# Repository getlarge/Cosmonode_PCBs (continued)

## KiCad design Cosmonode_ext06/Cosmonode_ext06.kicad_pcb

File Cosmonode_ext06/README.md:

# Cosmonode_ext_06

Extension 6  : - BNC connector for ph probe 
	       - 5V signal converted to 3.3V

Work in progress

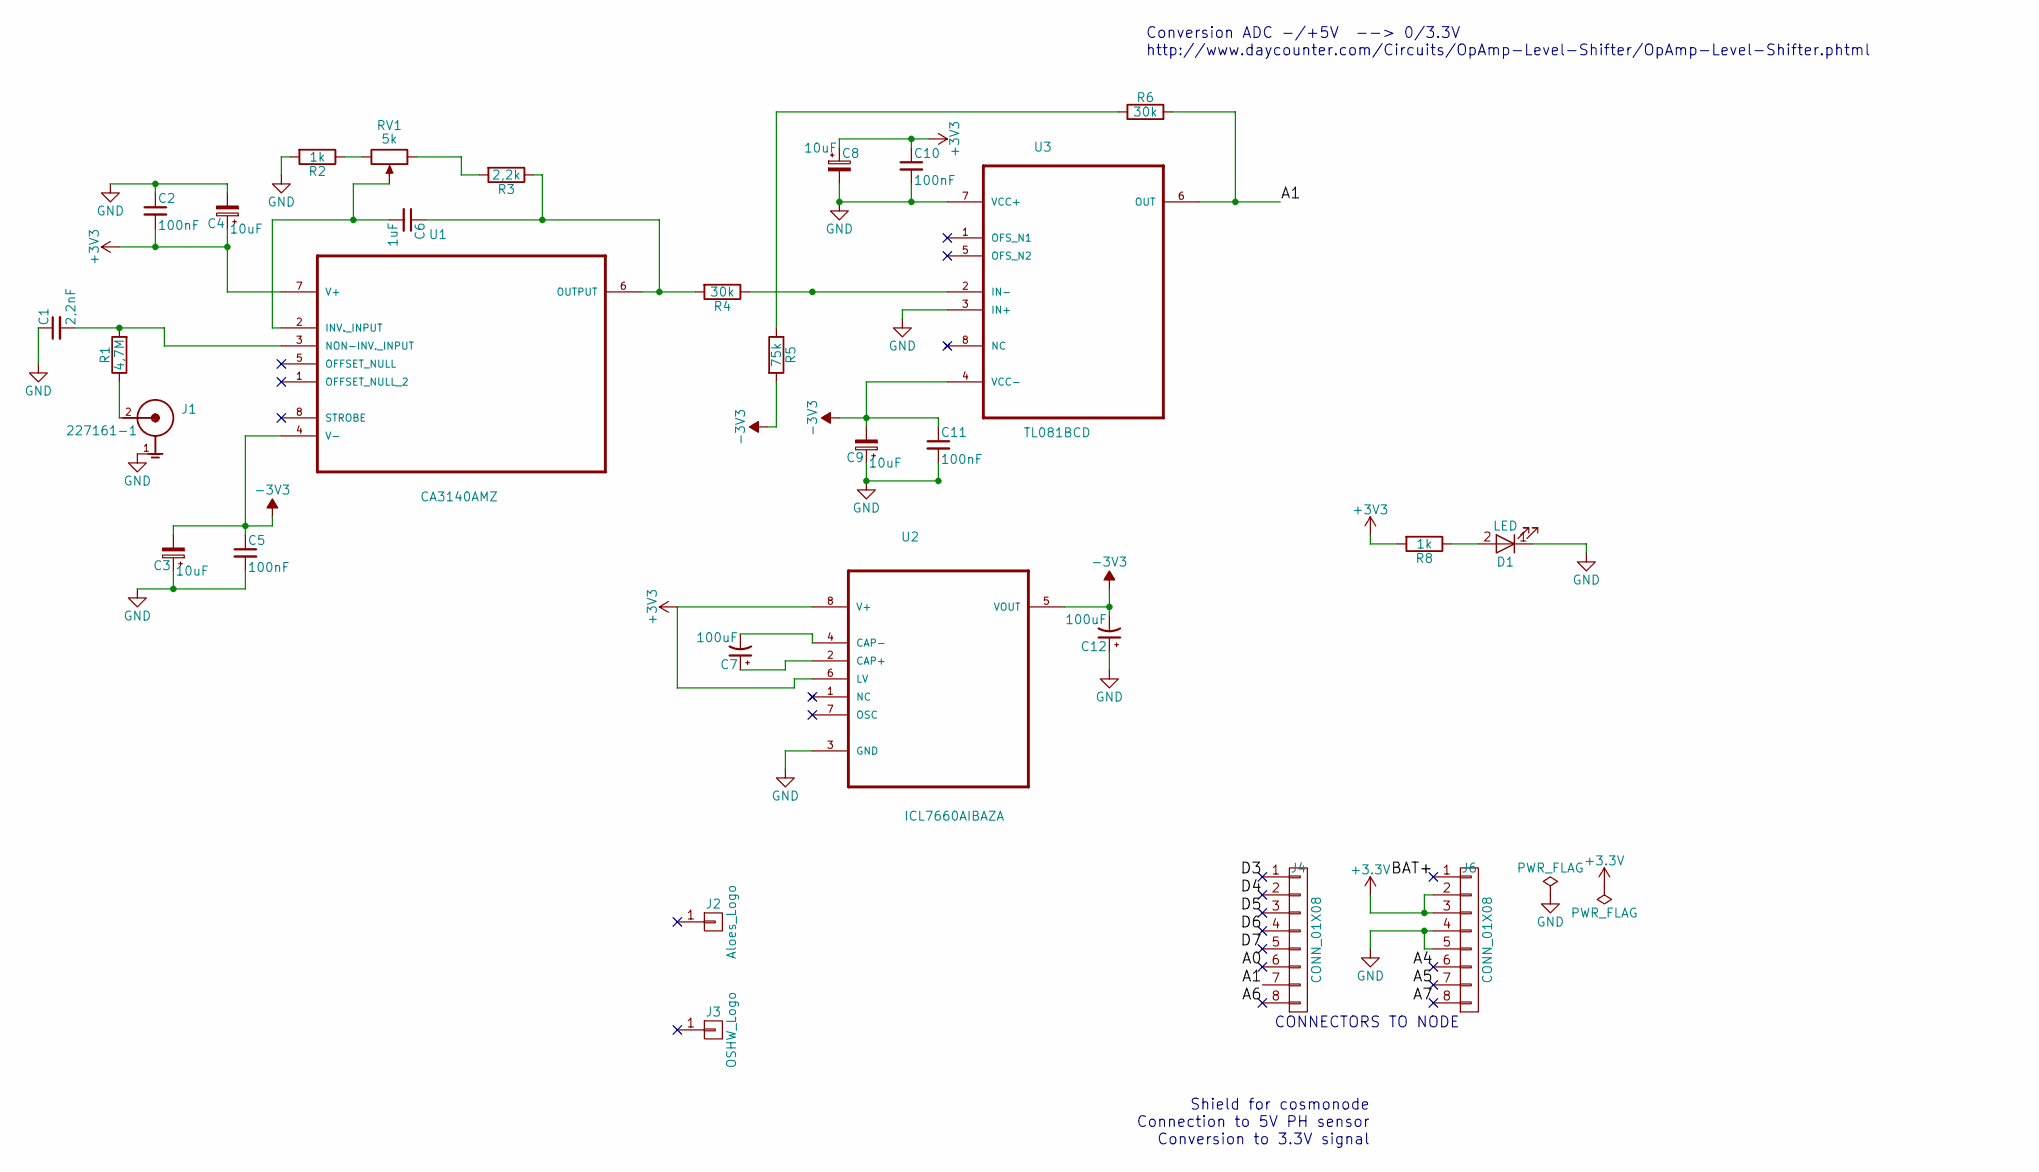
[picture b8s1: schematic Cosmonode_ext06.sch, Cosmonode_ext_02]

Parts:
C1: 2,2nF; C_0603_HandSoldering
C2, C5, C10, C11: 100nF; C_0603_HandSoldering
C3, C4, C8, C9: 10uF; C_0603_HandSoldering
C6: 1uF; C_0603_HandSoldering
C7, C12: 100uF; C_0603_HandSoldering
D1: LED; LED_0603_HandSoldering
J1: 227161-1; TE_227161-1
J2: Aloes_Logo; Aloes_mini
J3: OSHW_Logo; OSHW-Logo_5.7x6mm_SilkScreen
J4, J6: CONN_01X08; Socket_Strip_Straight_1x08_Pitch2.54mm
R1: 4,7M; R_0603_HandSoldering
R2, R8: 1k; R_0603_HandSoldering
R3: 2,2k; R_0603_HandSoldering
R4, R6: 30k; R_0603_HandSoldering
R5: 75k; R_0603_HandSoldering
RV1: 5k; Potentiometer_Trimmer_Bourns_3296W
U1: CA3140AMZ; SOIC-8_3.9x4.9mm_Pitch1.27mm
U2: ICL7660AIBAZA; SOIC-8_3.9x4.9mm_Pitch1.27mm
U3: TL081BCD; SOIC-8_3.9x4.9mm_Pitch1.27mm

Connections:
-3V3: C3.2, C5.1, C9.2, C11.1, C12.2, R5.2, U1.4 (V-), U2.5 (VOUT), U3.4 (VCC-)
/A0: J4.6
/A1: J4.7, R6.2, U3.6 (OUT)
/A4: J6.6
/A5: J6.7
/A6: J4.8
/A7: J6.8
/BAT+: J6.1
/D3: J4.1
/D4: J4.2
/D5: J4.3
/D6: J4.4
/D7: J4.5
GND: C1.1, C2.1, C3.1, C4.2, C5.2, C8.2, C9.1, C10.2, C11.2, C12.1, D1.1 (K), J1.1 (G), J6.4, J6.5, R2.2, U2.3 (GND), U3.3 (IN+), U3.7 (VCC+)
unnamed: C1.2, R1.2, U1.3 (NON-INV._INPUT)
unnamed: C6.1, R3.1, R4.2, U1.6 (OUTPUT)
unnamed: C6.2, RV1.2, U1.2 (INV._INPUT)
unnamed: C7.1, U2.2 (CAP+)
unnamed: C7.2, U2.4 (CAP-)
unnamed: D1.2 (A), R8.1
unnamed: J1.2 (C), R1.1
unnamed: R2.1, RV1.3
unnamed: R3.2, RV1.1
unnamed: R4.1, U3.2 (IN-)
unnamed: R5.1, R6.1

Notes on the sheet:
Shield for cosmonode Connection to 5V PH sensor Conversion to 3.3V signal
CONNECTORS TO NODE
Conversion ADC -/+5V --> 0/3.3V http://www.daycounter.com/Circuits/OpAmp-Level-Shifter/OpAmp-Level-Shifter.phtml

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
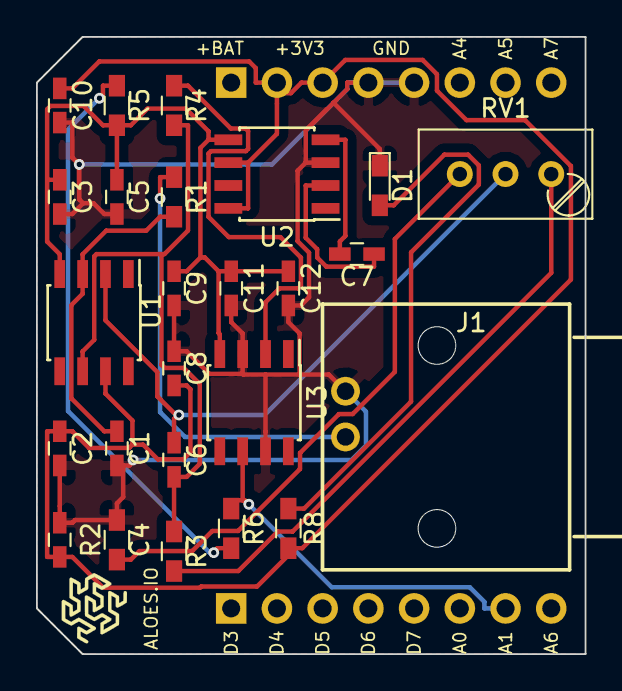
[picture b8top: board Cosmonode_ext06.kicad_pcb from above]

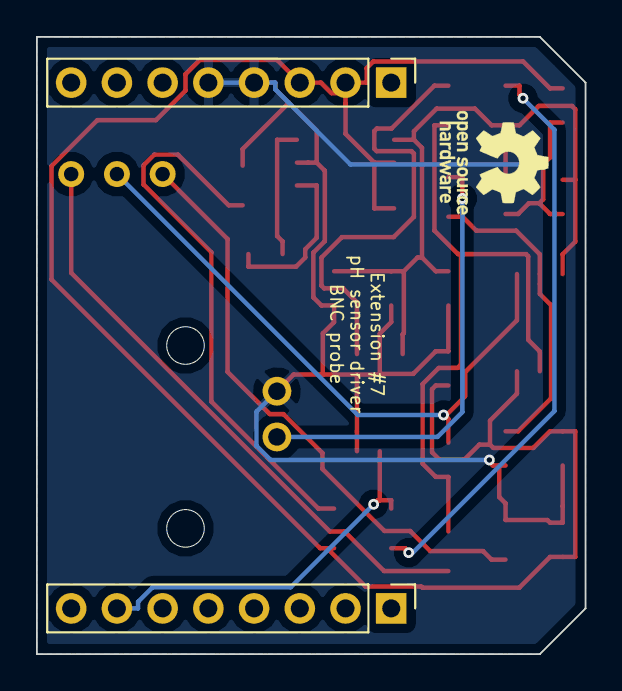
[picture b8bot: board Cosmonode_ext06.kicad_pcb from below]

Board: 2 copper layers, 30.5 x 34.3 mm, 29 parts (3 on the bottom side), 15 nets.

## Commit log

2017-08-19 add readme
2017-08-19 add inner Readmes
2017-09-21 micro update
2017-09-30 new version 0.3
2017-10-03 big push!
2017-10-04 big push2
2017-10-05 fully update to v0.3
2017-10-06 fix before test
2017-11-05 update to v0.5 ( base, ext05, ext07, ext08 )
2017-11-11 remove references
2017-12-07 update to V0.7 (WIP)
2017-12-11 near v0.7 ( mother and ext02 ), add mini extension
2017-12-11 renaming
2017-12-11 add picture
2017-12-20 fix and update
2017-12-20 test
